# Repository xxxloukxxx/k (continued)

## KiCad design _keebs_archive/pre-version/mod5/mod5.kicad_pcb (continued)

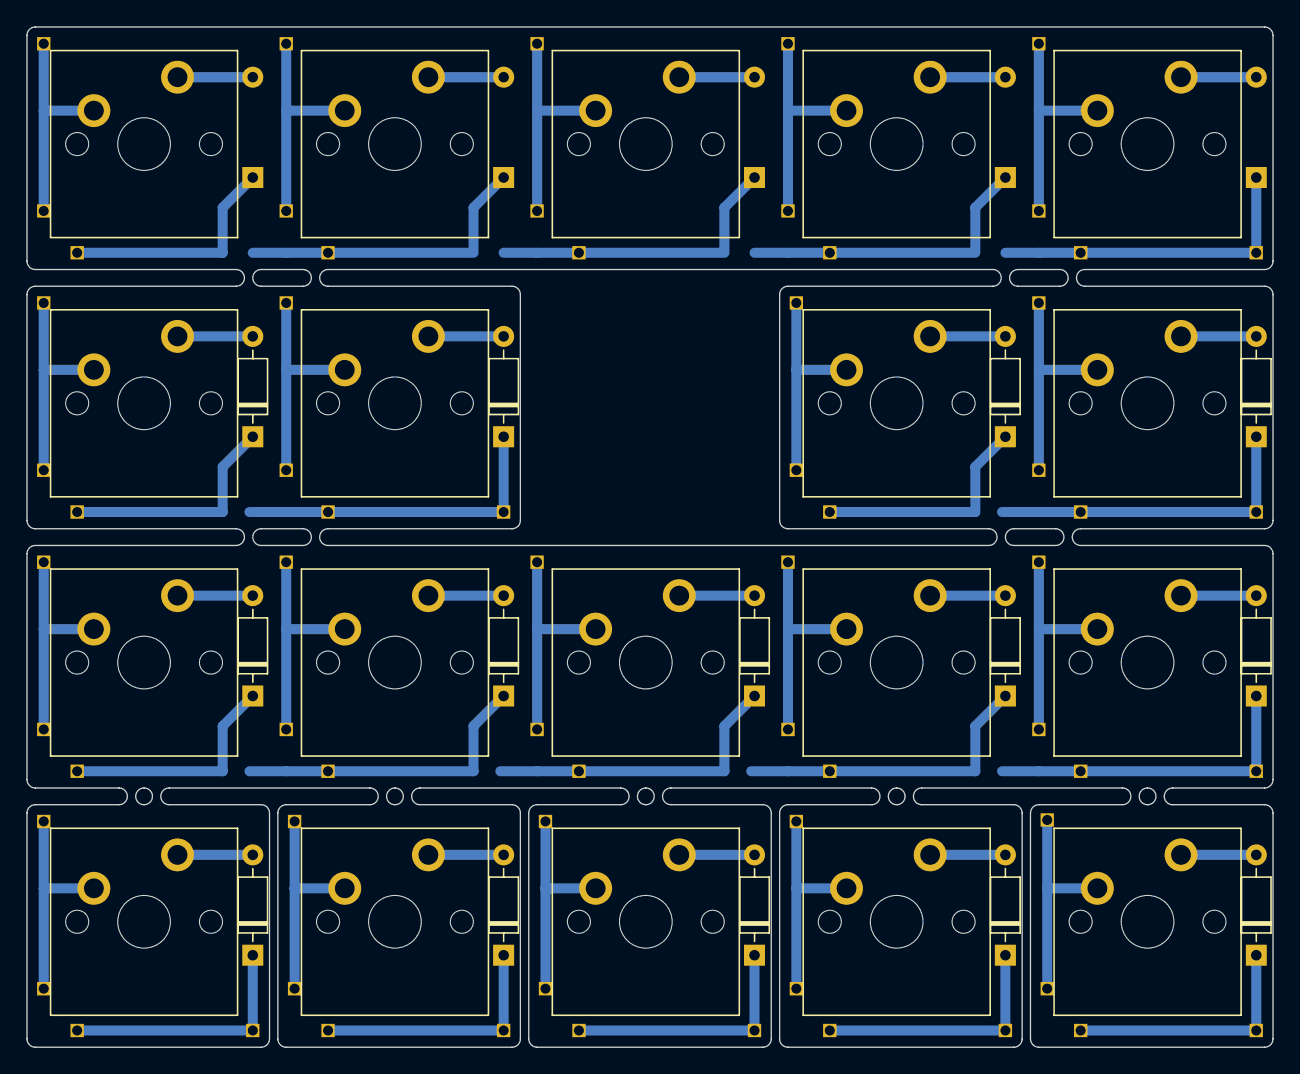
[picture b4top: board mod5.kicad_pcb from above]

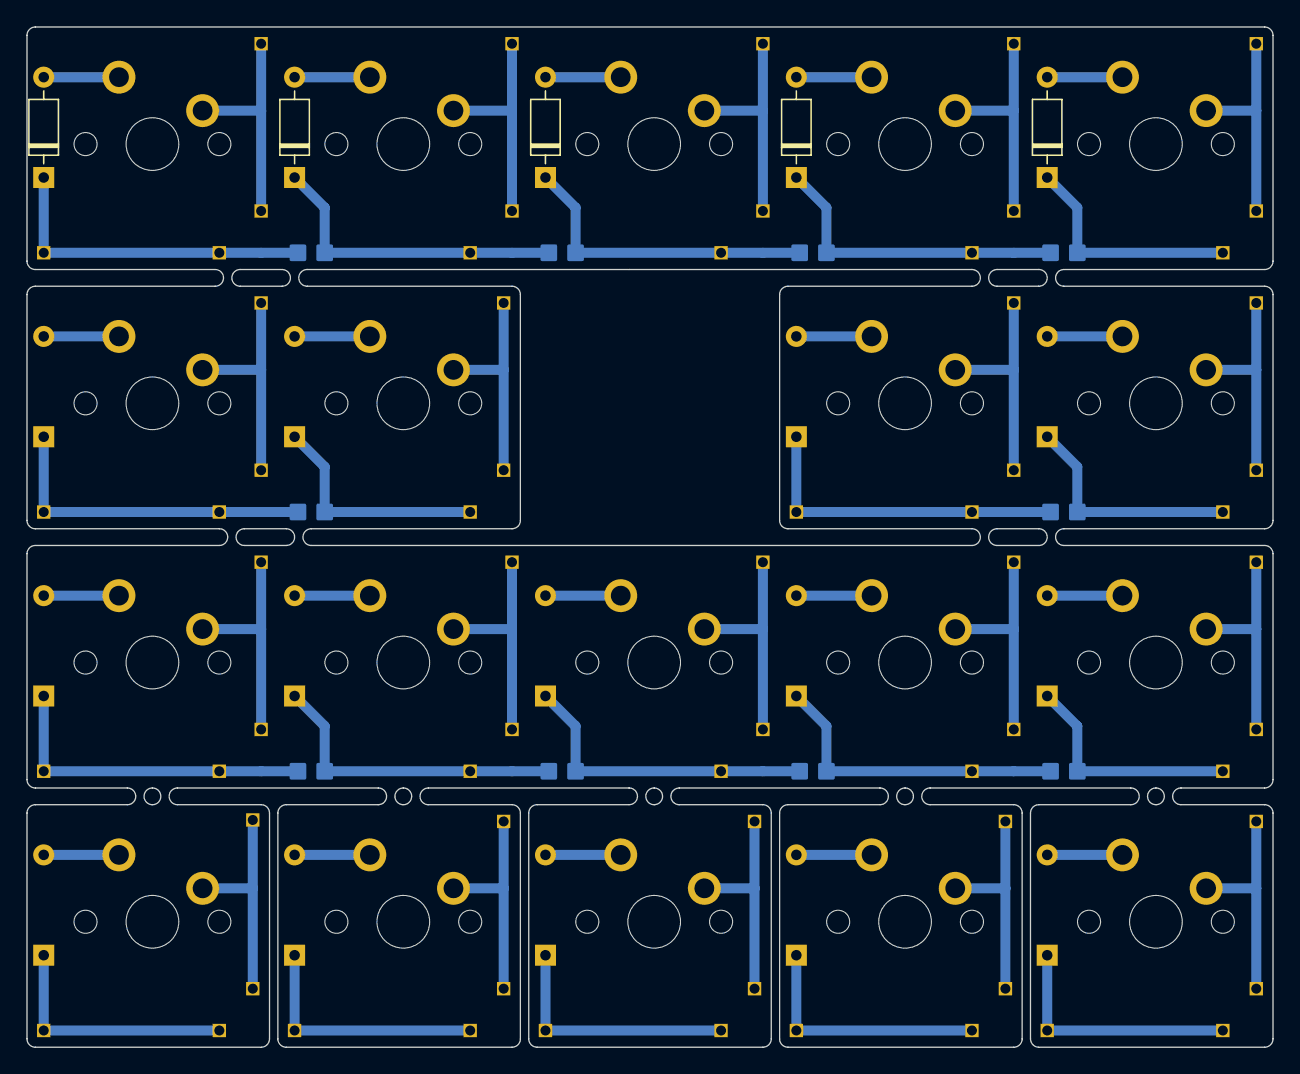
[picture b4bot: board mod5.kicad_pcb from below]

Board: 2 copper layers, 94.6 x 77.5 mm, 114 parts (5 on the bottom side), 57 nets.

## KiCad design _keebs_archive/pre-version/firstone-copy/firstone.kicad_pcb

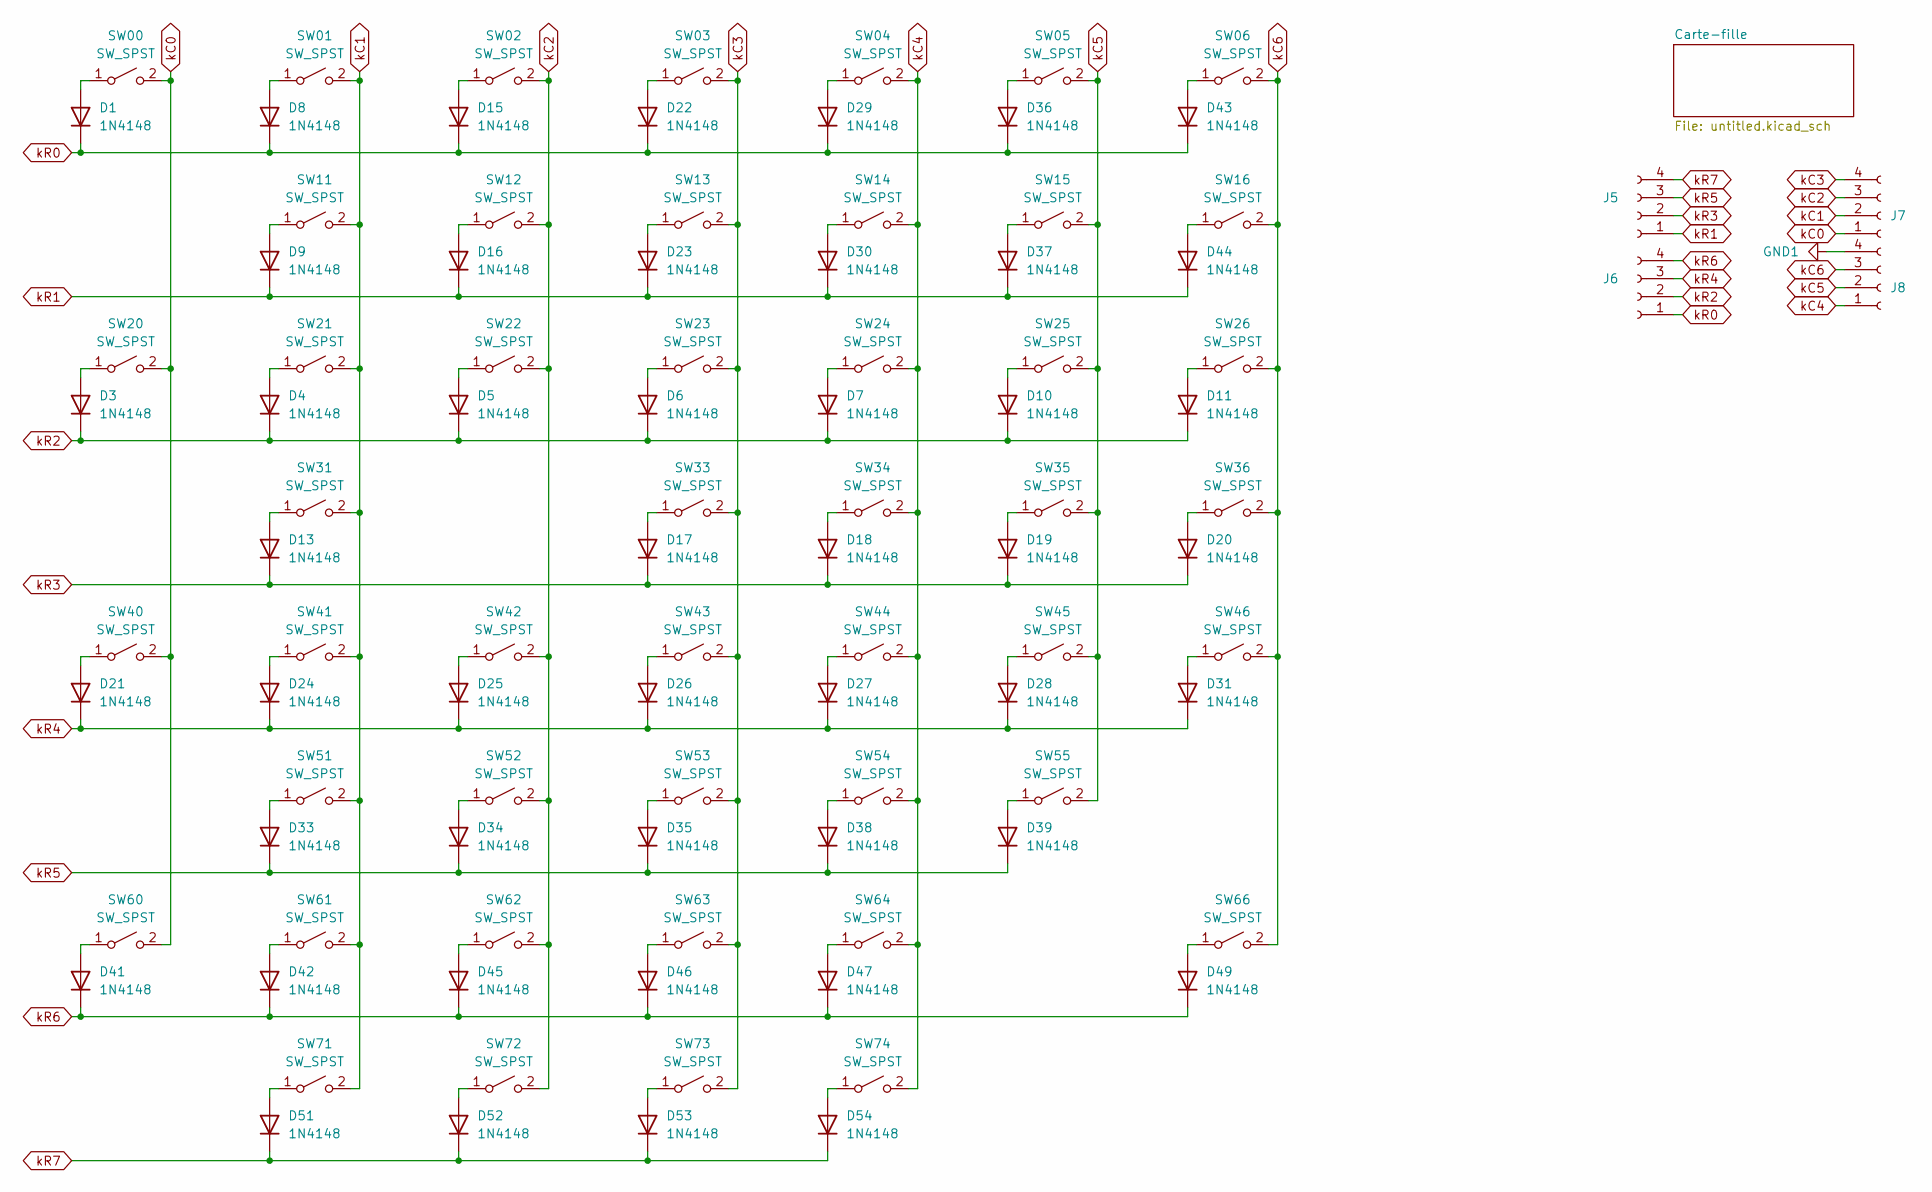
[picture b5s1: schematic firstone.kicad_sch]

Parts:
D1, D3, D4, D5, D6, D7, D8, D9, D10, D11, D13, D15, D16, D17, D18, D19, D20, D21, D22, D23, D24, D25, D26, D27, D28, D29, D30, D31, D33, D34, D35, D36, D37, D38, D39, D41, D42, D43, D44, D45, D46, D47, D49, D51, D52, D53, D54: 1N4148; D_DO-35_SOD27_P7.62mm_Horizontal
J5, J6, J7, J8: Conn_01x04_Socket; PinHeader_1x04_P2.54mm_Vertical
SW00, SW01, SW02, SW03, SW04, SW05, SW06, SW11, SW12, SW13, SW14, SW15, SW16, SW20, SW21, SW22, SW23, SW24, SW25, SW26, SW31, SW33, SW34, SW35, SW36, SW40, SW41, SW42, SW43, SW44, SW45, SW46, SW51, SW52, SW53, SW54, SW55, SW60, SW61, SW62, SW63, SW64, SW66, SW71, SW72, SW73, SW74: SW_SPST; SW_Cherry_MX_PCB

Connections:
GND1: J8.4
unnamed: D1.2 (A), SW00.1 (A)
unnamed: D3.2 (A), SW20.1 (A)
unnamed: D4.2 (A), SW21.1 (A)
unnamed: D5.2 (A), SW22.1 (A)
unnamed: D6.2 (A), SW23.1 (A)
unnamed: D7.2 (A), SW24.1 (A)
unnamed: D8.2 (A), SW01.1 (A)
unnamed: D9.2 (A), SW11.1 (A)
unnamed: D10.2 (A), SW25.1 (A)
unnamed: D11.2 (A), SW26.1 (A)
unnamed: D13.2 (A), SW31.1 (A)
unnamed: D15.2 (A), SW02.1 (A)
unnamed: D16.2 (A), SW12.1 (A)
unnamed: D17.2 (A), SW33.1 (A)
unnamed: D18.2 (A), SW34.1 (A)
unnamed: D19.2 (A), SW35.1 (A)
unnamed: D20.2 (A), SW36.1 (A)
unnamed: D21.2 (A), SW40.1 (A)
unnamed: D22.2 (A), SW03.1 (A)
unnamed: D23.2 (A), SW13.1 (A)
unnamed: D24.2 (A), SW41.1 (A)
unnamed: D25.2 (A), SW42.1 (A)
unnamed: D26.2 (A), SW43.1 (A)
unnamed: D27.2 (A), SW44.1 (A)
unnamed: D28.2 (A), SW45.1 (A)
unnamed: D29.2 (A), SW04.1 (A)
unnamed: D30.2 (A), SW14.1 (A)
unnamed: D31.2 (A), SW46.1 (A)
unnamed: D33.2 (A), SW51.1 (A)
unnamed: D34.2 (A), SW52.1 (A)
unnamed: D35.2 (A), SW53.1 (A)
unnamed: D36.2 (A), SW05.1 (A)
unnamed: D37.2 (A), SW15.1 (A)
unnamed: D38.2 (A), SW54.1 (A)
unnamed: D39.2 (A), SW55.1 (A)
unnamed: D41.2 (A), SW60.1 (A)
unnamed: D42.2 (A), SW61.1 (A)
unnamed: D43.2 (A), SW06.1 (A)
unnamed: D44.2 (A), SW16.1 (A)
unnamed: D45.2 (A), SW62.1 (A)
unnamed: D46.2 (A), SW63.1 (A)
unnamed: D47.2 (A), SW64.1 (A)
unnamed: D49.2 (A), SW66.1 (A)
unnamed: D51.2 (A), SW71.1 (A)
unnamed: D52.2 (A), SW72.1 (A)
unnamed: D53.2 (A), SW73.1 (A)
unnamed: D54.2 (A), SW74.1 (A)
kC0: J7.1, SW00.2 (B), SW20.2 (B), SW40.2 (B), SW60.2 (B)
kC1: J7.2, SW01.2 (B), SW11.2 (B), SW21.2 (B), SW31.2 (B), SW41.2 (B), SW51.2 (B), SW61.2 (B), SW71.2 (B)
kC2: J7.3, SW02.2 (B), SW12.2 (B), SW22.2 (B), SW42.2 (B), SW52.2 (B), SW62.2 (B), SW72.2 (B)
kC3: J7.4, SW03.2 (B), SW13.2 (B), SW23.2 (B), SW33.2 (B), SW43.2 (B), SW53.2 (B), SW63.2 (B), SW73.2 (B)
kC4: J8.1, SW04.2 (B), SW14.2 (B), SW24.2 (B), SW34.2 (B), SW44.2 (B), SW54.2 (B), SW64.2 (B), SW74.2 (B)
kC5: J8.2, SW05.2 (B), SW15.2 (B), SW25.2 (B), SW35.2 (B), SW45.2 (B), SW55.2 (B)
kC6: J8.3, SW06.2 (B), SW16.2 (B), SW26.2 (B), SW36.2 (B), SW46.2 (B), SW66.2 (B)
kR0: D1.1 (K), D8.1 (K), D15.1 (K), D22.1 (K), D29.1 (K), D36.1 (K), D43.1 (K), J6.1
kR1: D9.1 (K), D16.1 (K), D23.1 (K), D30.1 (K), D37.1 (K), D44.1 (K), J5.1
kR2: D3.1 (K), D4.1 (K), D5.1 (K), D6.1 (K), D7.1 (K), D10.1 (K), D11.1 (K), J6.2
kR3: D13.1 (K), D17.1 (K), D18.1 (K), D19.1 (K), D20.1 (K), J5.2
kR4: D21.1 (K), D24.1 (K), D25.1 (K), D26.1 (K), D27.1 (K), D28.1 (K), D31.1 (K), J6.3
kR5: D33.1 (K), D34.1 (K), D35.1 (K), D38.1 (K), D39.1 (K), J5.3
kR6: D41.1 (K), D42.1 (K), D45.1 (K), D46.1 (K), D47.1 (K), D49.1 (K), J6.4
kR7: D51.1 (K), D52.1 (K), D53.1 (K), D54.1 (K), J5.4

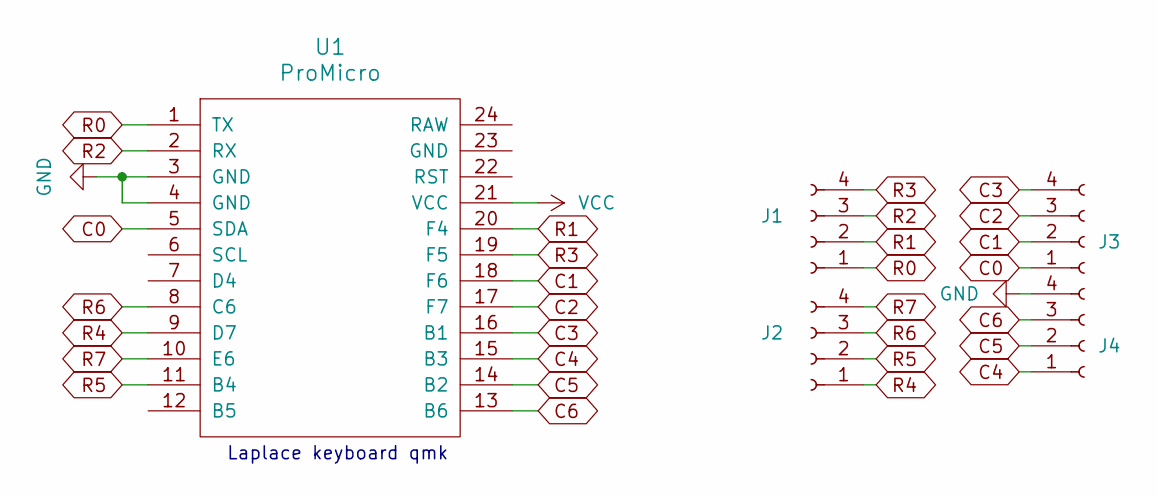
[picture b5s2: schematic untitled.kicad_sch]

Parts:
J1, J2, J3, J4: Conn_01x04_Socket; PinHeader_1x04_P2.54mm_Horizontal
U1: ProMicro

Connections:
C0: J3.1, U1.5 (SDA)
C1: J3.2, U1.18 (F6)
C2: J3.3, U1.17 (F7)
C3: J3.4, U1.16 (B1)
C4: J4.1, U1.15 (B3)
C5: J4.2, U1.14 (B2)
C6: J4.3, U1.13 (B6)
GND: J4.4, U1.3 (GND), U1.4 (GND)
R0: J1.1, U1.1 (TX)
R1: J1.2, U1.20 (F4)
R2: J1.3, U1.2 (RX)
R3: J1.4, U1.19 (F5)
R4: J2.1, U1.9 (D7)
R5: J2.2, U1.11 (B4)
R6: J2.3, U1.8 (C6)
R7: J2.4, U1.10 (E6)
VCC: U1.21 (VCC)

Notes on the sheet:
Laplace keyboard qmk

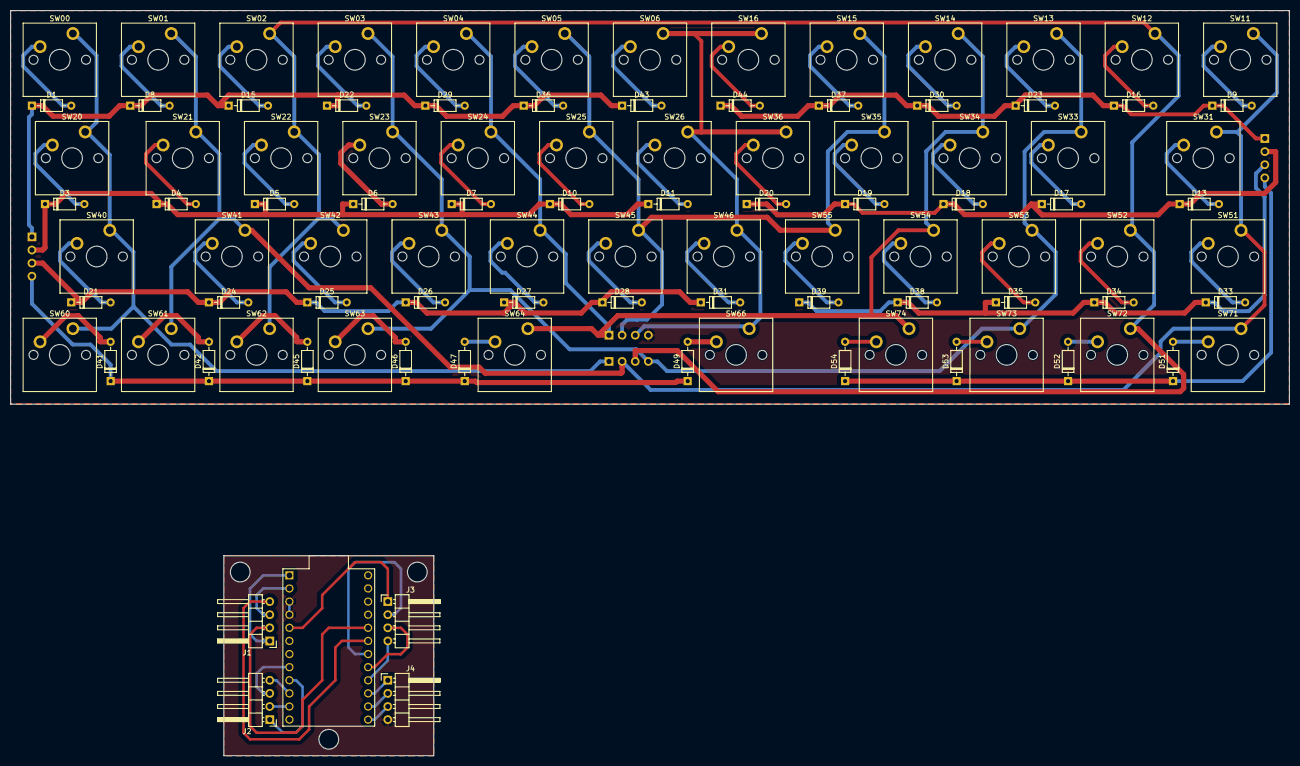
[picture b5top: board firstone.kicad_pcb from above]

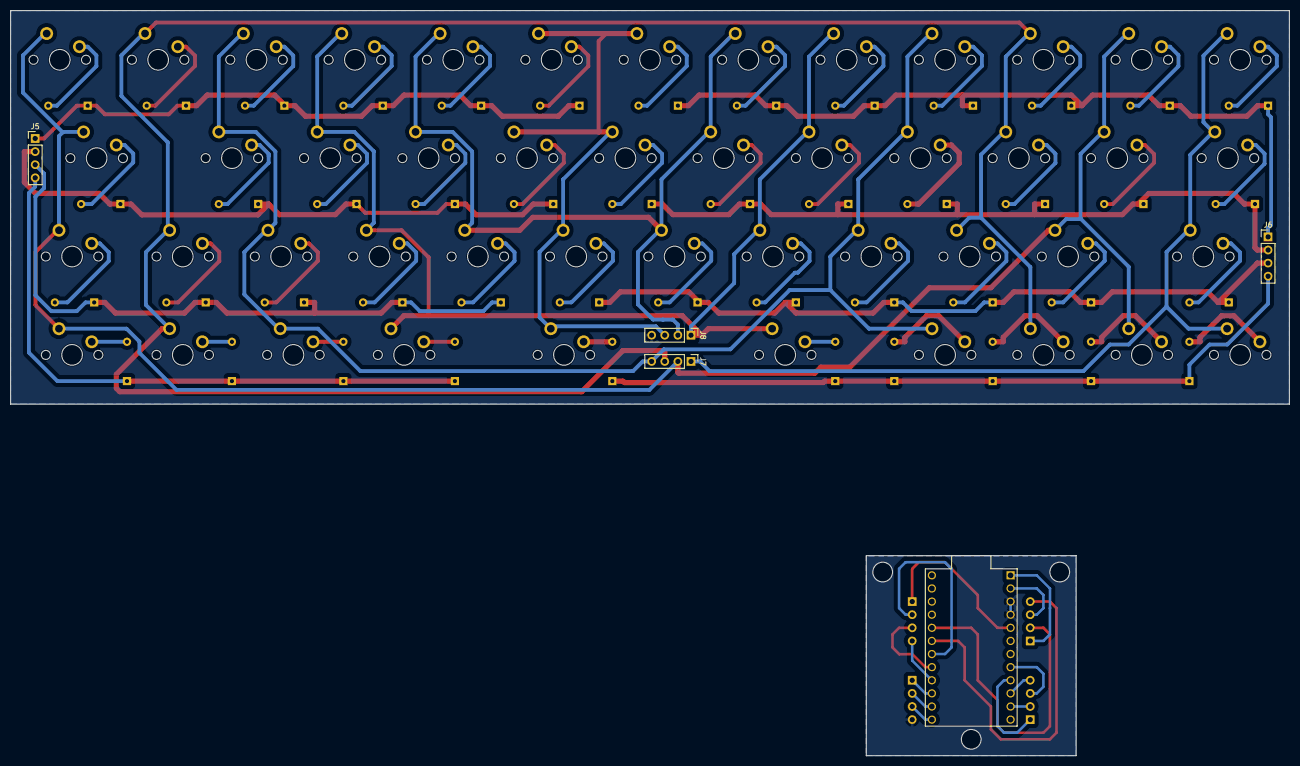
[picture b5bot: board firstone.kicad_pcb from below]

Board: 2 copper layers, 247.6 x 76.2 mm, 103 parts (4 on the bottom side), 78 nets.

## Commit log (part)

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2024-03-10 dim. 10 mars 2024 22:28:26 CET
2024-03-10 dim. 10 mars 2024 23:07:29 CET
2024-03-16 sam. 16 mars 2024 15:41:34 CET
2024-03-16 sam. 16 mars 2024 20:01:37 CET
2024-03-17 dim. 17 mars 2024 09:56:18 CET
2024-03-17 dim. 17 mars 2024 13:03:14 CET
2024-03-27 mer. 27 mars 2024 07:01:20 CET
2024-05-08 mer. 08 mai 2024 13:53:09 CEST
2024-05-08 mer. 08 mai 2024 14:19:52 CEST
2024-05-17 ven. 17 mai 2024 09:59:28 CEST
2024-05-20 lun. 20 mai 2024 22:03:54 CEST
2024-05-21 mar. 21 mai 2024 07:01:33 CEST
2024-05-21 mar. 21 mai 2024 08:07:23 CEST
2024-05-27 lun. 27 mai 2024 10:43:09 CEST
2024-05-27 lun. 27 mai 2024 07:07:30 CEST
2024-05-28 mar. 28 mai 2024 07:28:23 CEST
2024-05-29 mer. 29 mai 2024 13:42:54 CEST
2024-06-01 sam. 01 juin 2024 20:48:59 CEST
2024-06-01 dim. 02 juin 2024 00:18:32 CEST
2024-06-01 dim. 02 juin 2024 00:46:11 CEST
2024-06-02 dim. 02 juin 2024 13:01:29 CEST
2024-06-04 erzzer
2024-06-06 jeu. 06 juin 2024 06:28:55 CEST
2024-06-08 sam. 08 juin 2024 21:05:04 CEST
2024-06-11 mar. 11 juin 2024 15:38:36 CEST
2024-06-16 dim. 16 juin 2024 11:32:44 CEST
2024-06-20 jeu. 20 juin 2024 16:58:49 CEST
2024-06-21 plop
2024-06-21 ven. 21 juin 2024 17:28:28 CEST
2024-06-26 mer. 26 juin 2024 09:22:50 CEST
2024-06-30 dim. 30 juin 2024 21:13:07 CEST
2024-07-03 mer. 03 juil. 2024 14:16:50 CEST
2024-07-11 jeu. 11 juil. 2024 14:02:05 CEST
2024-07-12 ven. 12 juil. 2024 08:59:38 CEST
2024-07-13 sam. 13 juil. 2024 16:38:29 CEST
2024-07-13 sam. 13 juil. 2024 18:44:23 CEST
2024-07-13 sam. 13 juil. 2024 18:45:01 CEST
2024-07-14 dim. 14 juil. 2024 23:47:23 CEST
2024-07-15 lun. 15 juil. 2024 17:34:45 CEST
2024-07-29 mar. 30 juil. 2024 00:01:51 CEST
2024-08-25 dim. 25 août 2024 15:27:40 CEST
2024-08-28 mer. 28 août 2024 16:14:43 CEST
2024-08-29 jeu. 29 août 2024 19:49:08 CEST
2024-09-15 dim. 15 sept. 2024 15:09:34 CEST
2024-09-17 mar. 17 sept. 2024 21:54:07 CEST
2024-09-22 dim. 22 sept. 2024 20:45:59 CEST
2024-10-16 mer. 16 oct. 2024 06:54:32 CEST
2024-10-16 mer. 16 oct. 2024 21:30:50 CEST
2024-10-18 ven. 18 oct. 2024 07:16:40 CEST
2024-10-19 sam. 19 oct. 2024 14:43:41 CEST
2024-10-19 sam. 19 oct. 2024 18:38:35 CEST
2024-10-20 dim. 20 oct. 2024 11:46:04 CEST
2024-10-23 mer. 23 oct. 2024 11:17:43 CEST
2024-10-23 mer. 23 oct. 2024 17:10:08 CEST
2024-10-23 mer. 23 oct. 2024 20:45:41 CEST
2024-10-23 mer. 23 oct. 2024 22:37:45 CEST
2024-10-23 mer. 23 oct. 2024 22:58:46 CEST
2024-10-24 jeu. 24 oct. 2024 10:44:25 CEST
2024-10-24 jeu. 24 oct. 2024 17:43:03 CEST
2025-01-22 mer. 22 janv. 2025 18:12:13 CET
2025-01-24 ven. 24 janv. 2025 23:25:14 CET
2025-01-25 sam. 25 janv. 2025 13:10:40 CET
2025-01-25 sam. 25 janv. 2025 13:35:42 CET
2025-01-28 mar. 28 janv. 2025 23:41:58 CET
2025-01-30 jeu. 30 janv. 2025 17:31:28 CET
2025-01-30 ven. 31 janv. 2025 00:37:18 CET
2025-01-31 ven. 31 janv. 2025 15:56:43 CET
2025-02-01 sam. 01 févr. 2025 13:03:55 CET
2025-02-04 mar. 04 févr. 2025 09:30:06 CET
2025-02-05 mer. 05 févr. 2025 17:14:07 CET
2025-02-05 mer. 05 févr. 2025 21:44:44 CET
2025-02-06 jeu. 06 févr. 2025 20:25:15 CET
2025-02-16 dim. 16 févr. 2025 18:15:23 CET
2025-02-19 mer. 19 févr. 2025 10:49:13 CET
2025-02-19 mer. 19 févr. 2025 18:15:28 CET
2025-02-20 jeu. 20 févr. 2025 20:27:44 CET
2025-02-20 jeu. 20 févr. 2025 20:02:27 CET
2025-03-08 sam. 08 mars 2025 15:02:32 CET
2025-03-08 sam. 08 mars 2025 15:21:17 CET
2025-03-08 sam. 08 mars 2025 16:55:18 CET
2025-03-09 dim. 09 mars 2025 16:57:42 CET
2025-03-09 dim. 09 mars 2025 16:59:08 CET
2025-03-09 dim. 09 mars 2025 20:54:32 CET
2025-03-10 lun. 10 mars 2025 07:18:12 CET
2025-03-10 lun. 10 mars 2025 07:18:27 CET
2025-03-31 lun. 31 mars 2025 22:10:16 CEST
2025-03-31 lun. 31 mars 2025 22:10:31 CEST
2025-03-31 lun. 31 mars 2025 22:14:03 CEST
2025-04-02 mer. 02 avril 2025 12:03:43 CEST
2025-04-24 jeu. 24 avril 2025 22:57:20 CEST
2025-04-24 jeu. 24 avril 2025 23:41:24 CEST
2025-04-24 jeu. 24 avril 2025 23:47:25 CEST
2025-05-10 sam. 10 mai 2025 09:34:07 CEST
2025-05-10 sam. 10 mai 2025 19:39:14 CEST
2025-05-11 dim. 11 mai 2025 22:27:50 CEST
2025-05-11 dim. 11 mai 2025 22:54:30 CEST
2025-05-13 mar. 13 mai 2025 05:38:26 CEST
2025-05-14 mer. 14 mai 2025 15:30:07 CEST
2025-05-14 mer. 14 mai 2025 15:32:31 CEST
2025-05-16 ven. 16 mai 2025 08:39:46 CEST
2025-05-18 dim. 18 mai 2025 21:00:05 CEST
2025-05-21 mer. 21 mai 2025 14:28:08 CEST
2025-05-25 dim. 25 mai 2025 13:40:57 CEST
2025-05-25 dim. 25 mai 2025 13:41:52 CEST
2025-05-30 ven. 30 mai 2025 13:18:21 CEST
2025-05-30 ven. 30 mai 2025 13:18:54 CEST
2025-05-30 ven. 30 mai 2025 13:27:21 CEST
2025-05-30 ven. 30 mai 2025 13:42:43 CEST
2025-05-30 ven. 30 mai 2025 23:04:41 CEST
2025-06-04 mer. 04 juin 2025 17:11:12 CEST
2025-06-14 sam. 14 juin 2025 15:33:43 CEST
2025-06-15 dim. 15 juin 2025 16:50:42 CEST
2025-06-15 dim. 15 juin 2025 18:40:32 CEST
2025-06-20 Mise à jour keymap
2025-07-16 mer. 16 juil. 2025 16:52:14 CEST
2025-07-25 ven. 25 juil. 2025 15:41:56 CEST
2025-07-31 jeu. 31 juil. 2025 20:50:20 CEST
2025-07-31 jeu. 31 juil. 2025 20:57:18 CEST
2025-08-21 jeu. 21 août 2025 20:33:50 CEST
2025-08-27 mise à jour
2025-08-27 mer. 27 août 2025 13:02:14 CEST
2025-09-04 jeu. 04 sept. 2025 19:50:23 CEST
2025-09-08 lun. 08 sept. 2025 13:16:26 CEST
2025-10-07 mar. 07 oct. 2025 14:34:33 CEST
2025-10-20 lun. 20 oct. 2025 14:38:09 CEST
2025-10-29 mer. 29 oct. 2025 15:25:05 CET
2025-10-29 mer. 29 oct. 2025 15:21:21 CET
2025-11-09 dim. 09 nov. 2025 15:22:23 CET
2025-12-21 dim. 21 déc. 2025 17:40:23 CET
2025-12-30 mar. 30 déc. 2025 02:12:28 CET
2026-01-06 mar. 06 janv. 2026 23:18:08 CET
2026-02-10 add altgr
